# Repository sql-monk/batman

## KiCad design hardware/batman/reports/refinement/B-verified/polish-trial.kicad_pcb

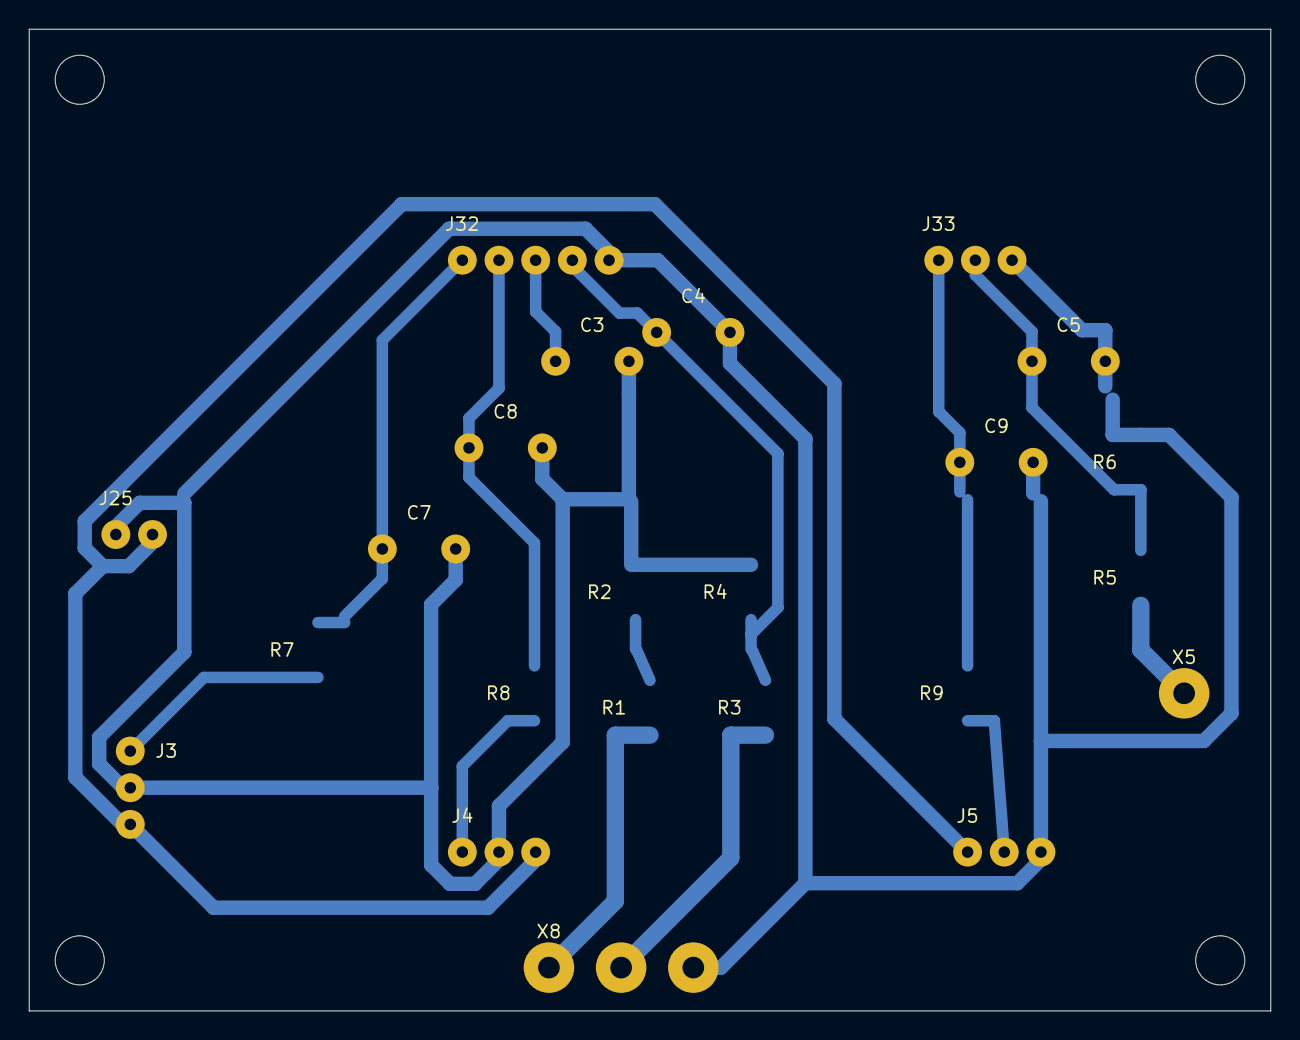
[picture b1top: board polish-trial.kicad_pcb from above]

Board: 2 copper layers, 86.0 x 68.0 mm, 28 parts (0 on the bottom side), 14 nets.

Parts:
C3: 100n_50V; LUT_C3
C4: 100n_50V; LUT_C4
C5: 100n_50V; LUT_C5
C7: 1u_16V; LUT_C7
C8: 1u_16V; LUT_C8
C9: 1u_16V; LUT_C9
HB1, HB2, HB3, HB4: M3_NPTH_3.4; Mount_M3
J3: ACS1_3WIRE; LUT_J3
J4: ACS2_3WIRE; LUT_J4
J5: ACS3_3WIRE; LUT_J5
J25: LINK_GND_+3V3_SENS; LUT_J25
J32: LINK_I_B1_I_B2_U_B1_U_B2_GND; LUT_J32
J33: LINK_I_LOAD_U_LOAD_GND; LUT_J33
R1: 100k_1%; LUT_R1
R2: 10k_1%; LUT_R2
R3: 100k_1%; LUT_R3
R4: 10k_1%; LUT_R4
R5: 100k_1%; LUT_R5
R6: 4.7k_1%; LUT_R6
R7: 1k; LUT_R7
R8: 1k; LUT_R8
R9: 1k; LUT_R9
WB1: INSULATED_WIRE; LUT_WB1
X5: U_LOAD_SENSE; LUT_X5
X8: BAT_SENSE_FROM_D; LUT_X8

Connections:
+3V3_SENS: J3.3, J4.3, J5.1, J25.2
B1: R1.1, X8.1
B2: R3.1, X8.2
GND: C3.2, C4.2, C5.2, C7.2, C8.2, C9.2, J3.2, J4.2, J5.3, J25.1, J32.5, J33.3, R2.2, R4.2, R6.2, X8.3
I_B1: C7.1, J32.1, R7.2
I_B2: C8.1, J32.2, R8.2
I_LOAD: C9.1, J33.1, R9.2
I_RAW1: J3.1, R7.1
I_RAW2: J4.1, R8.1
I_RAW3: J5.2, R9.1
LOAD+: R5.1, X5.1
U_B1: C3.1, J32.3, R1.2, R2.1, WB1.1
U_B2: C4.1, J32.4, R3.2, R4.1
U_LOAD: C5.1, J33.2, R5.2, R6.1

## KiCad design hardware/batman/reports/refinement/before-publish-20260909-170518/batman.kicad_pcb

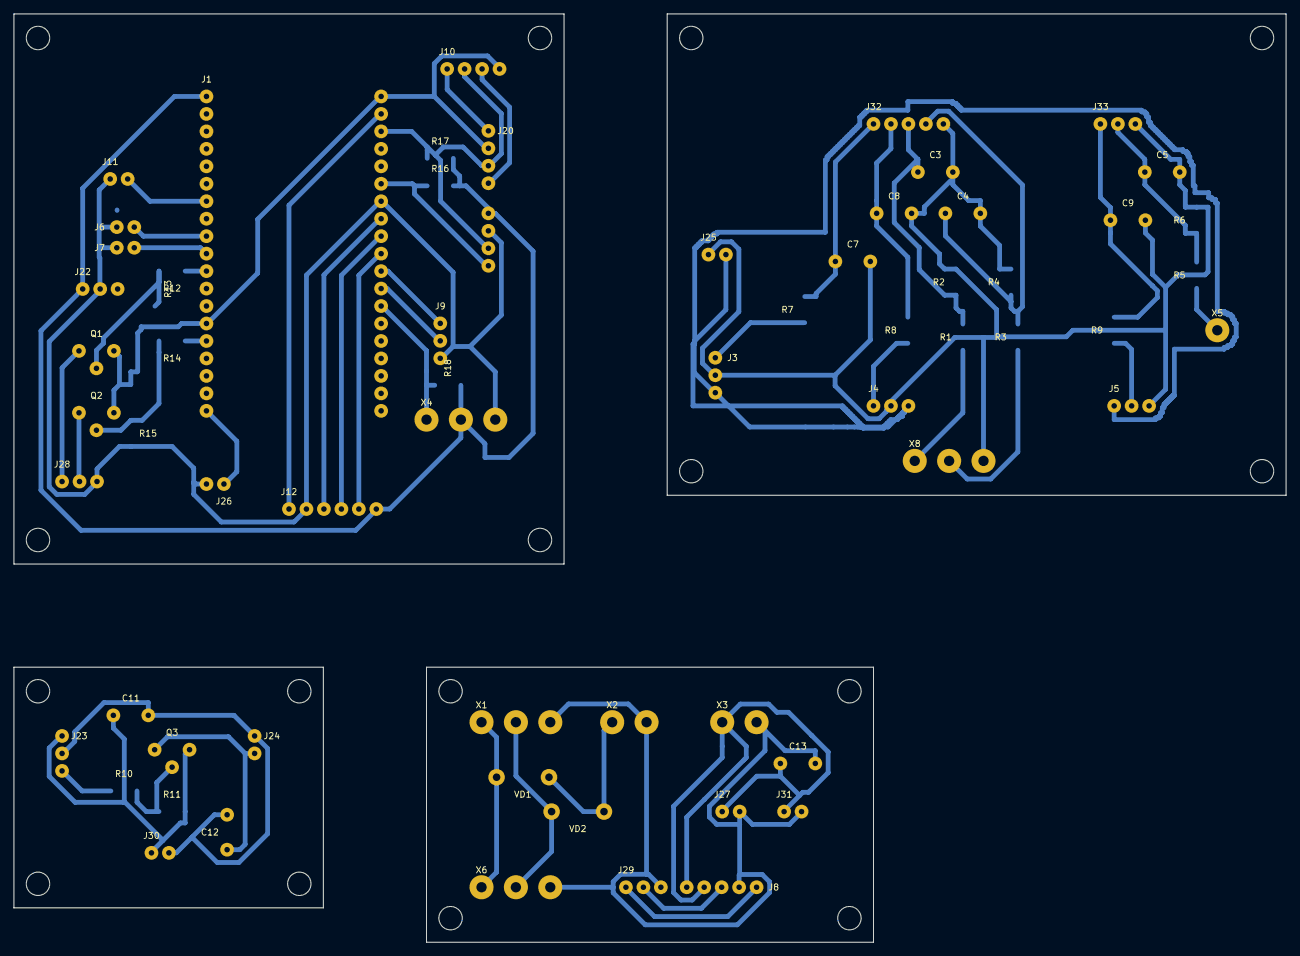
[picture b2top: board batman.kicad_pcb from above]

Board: 2 copper layers, 185.0 x 135.0 mm, 97 parts (0 on the bottom side), 39 nets.

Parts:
C3: 100n_50V; LUT_C3
C4: 100n_50V; LUT_C4
C5: 100n_50V; LUT_C5
C7: 1u_16V; LUT_C7
C8: 1u_16V; LUT_C8
C9: 1u_16V; LUT_C9
C11: 100n_16V; LUT_C11
C12: 100n_16V; LUT_C12
C13: 100n_16V; LUT_C13
HA1, HA2, HA3, HA4: M3_NPTH_3.4; Mount_M3
HB1, HB2, HB3, HB4: M3_NPTH_3.4; Mount_M3
HC1, HC2, HC3, HC4: M3_NPTH_3.4; Mount_M3
HD1, HD2, HD3, HD4: M3_NPTH_3.4; Mount_M3
J1: DevKitC_38_socket_mMCU; LUT_J1
J3: ACS1_3WIRE; LUT_J3
J4: ACS2_3WIRE; LUT_J4
J5: ACS3_3WIRE; LUT_J5
J6: SW1_GND_ON; LUT_J6
J7: SW2_GND_ON; LUT_J7
J8: RELAY; LUT_J8
J9: DPS_UART; LUT_J9
J10: OLED_I2C; LUT_J10
J11: BUTTON; LUT_J11
J12: SPI; LUT_J12
J20: LINK_+3V3_GND_SCL_SDA; LUT_J20
J21: LINK_+3V3_GND_SCL_SDA; LUT_J21
J22: LINK_+3V3_GND_SENS_PWR; LUT_J22
J23: LINK_+3V3_GND_SENS_PWR; LUT_J23
J24: LINK_GND_+3V3_SENS; LUT_J24
J25: LINK_GND_+3V3_SENS; LUT_J25
J26: LINK_+5V_GND; LUT_J26
J27: LINK_+5V_GND; LUT_J27
J28: LINK_RELAY_IN1_RELAY_IN2_GND; LUT_J28
J29: LINK_RELAY_IN1_RELAY_IN2_GND; LUT_J29
J30: LINK_+3V3_GND; LUT_J30
J31: LINK_+5V_GND; LUT_J31
J32: LINK_I_B1_I_B2_U_B1_U_B2_GND; LUT_J32
J33: LINK_I_LOAD_U_LOAD_GND; LUT_J33
NT1: COPPER_STAR_AT_X3; LUT_NT1
Q1: BC547_CBE; LUT_Q1
Q2: BC547_CBE; LUT_Q2
Q3: BC557_CBE; LUT_Q3
R1: 100k_1%; LUT_R1
R2: 10k_1%; LUT_R2
R3: 100k_1%; LUT_R3
R4: 10k_1%; LUT_R4
R5: 100k_1%; LUT_R5
R6: 4.7k_1%; LUT_R6
R7: 1k; LUT_R7
R8: 1k; LUT_R8
R9: 1k; LUT_R9
R10: 4.7k; LUT_R10
R11: 10k; LUT_R11
R12: 1k; LUT_R12
R13: 10k; LUT_R13
R14: 1k; LUT_R14
R15: 10k; LUT_R15
R16: 4.7k; LUT_R16
R17: 4.7k; LUT_R17
R18: 4.7k; LUT_R18
VD1: 1N5819; LUT_VD1
VD2: 1N5819; LUT_VD2
WA1: INSULATED_WIRE; LUT_WA1
WA2: INSULATED_WIRE; LUT_WA2
WA3: INSULATED_WIRE; LUT_WA3
WC2_1: EXTERNAL_CABLE_NOT_PCB; LUT_WC2_1
WC2_2: EXTERNAL_CABLE_NOT_PCB; LUT_WC2_2
WC2_3: EXTERNAL_CABLE_NOT_PCB; LUT_WC2_3
WC3_1: EXTERNAL_CABLE_NOT_PCB; LUT_WC3_1
WC3_2: EXTERNAL_CABLE_NOT_PCB; LUT_WC3_2
WC4_1: EXTERNAL_CABLE_NOT_PCB; LUT_WC4_1
WC4_2: EXTERNAL_CABLE_NOT_PCB; LUT_WC4_2
WC5_1: EXTERNAL_CABLE_NOT_PCB; LUT_WC5_1
WC5_2: EXTERNAL_CABLE_NOT_PCB; LUT_WC5_2
WC5_3: EXTERNAL_CABLE_NOT_PCB; LUT_WC5_3
WC6_1: EXTERNAL_CABLE_NOT_PCB; LUT_WC6_1
WC6_2: EXTERNAL_CABLE_NOT_PCB; LUT_WC6_2
WC6_3: EXTERNAL_CABLE_NOT_PCB; LUT_WC6_3
X1: B1_B2_GND; LUT_X1
X2: VIN_DC_GND; LUT_X2
X3: 5V_GND; LUT_X3
X4: DS18B20; LUT_X4
X5: U_LOAD_SENSE; LUT_X5
X6: BAT_SENSE_TO_B; LUT_X6
X8: BAT_SENSE_FROM_D; LUT_X8

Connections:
+3V3: C11.1, J1.1, J10.1, J12.6, J20.1, J21.1, J22.1, J23.1, J30.1, Q3.3, R11.2, R16.2, R17.2, R18.2, WA1.1, WC2_1.1, X4.2
+3V3_SENS: C12.1, J3.3, J4.3, J5.1, J24.2, J25.2, Q3.1, WC3_2.1
+5V: C13.1, J1.19, J26.1, J27.1, J31.1, NT1.1, WC4_1.1, X3.1
+5V_RELAY_COIL: J8.5, NT1.3
+5V_RELAY_VCC: J8.4, NT1.2
B1: R1.1, VD1.2, WC6_1.1, X1.1, X6.1, X8.1
B2: R3.1, VD2.2, WC6_2.1, X1.2, X6.2, X8.2
BASE1: Q1.2, R12.2, R13.1
BASE2: Q2.2, R14.2, R15.1
BASE3: Q3.2, R10.2, R11.1
BTN: J1.7, J11.2
CS: J1.29, J12.5
DPS_RX: J1.31, J9.2
DPS_TX: J1.30, J9.1
GND: C3.2, C4.2, C5.2, C7.2, C8.2, C9.2, C11.2, C12.2, C13.2, J1.14, J1.20, J1.26, J3.2, J4.2, J5.3, J6.1, J7.1, J8.2, J9.3, J10.4, J11.1, J12.2, J20.2, J21.2, J22.2, J23.2, J24.1, J25.1, J26.2, J27.2, J28.3, J29.3, J30.2, J31.2, J32.5, J33.3, Q1.3, Q2.3, R2.2, R4.2, R6.2, R13.2, R15.2, WC2_2.1, WC3_1.1, WC4_2.1, WC5_3.1, WC6_3.1, X1.3, X2.2, X3.2, X4.3, X6.3, X8.3
I_B1: C7.1, J32.1, R7.2
I_B2: C8.1, J32.2, R8.2
I_LOAD: C9.1, J33.1, R9.2
I_RAW1: J3.1, R7.1
I_RAW2: J4.1, R8.1
I_RAW3: J5.2, R9.1
K1: J1.11, R12.1
K2: J1.15, R14.1
LOAD+: R5.1, X5.1
MISO: J1.27, J12.3
MOSI: J1.21, J12.1
OW: J1.32, R18.1, X4.1
RELAY_IN1: J8.1, J28.1, J29.1, Q1.1, WC5_1.1
RELAY_IN2: J8.3, J28.2, J29.2, Q2.1, WC5_2.1
SCK: J1.28, J12.4
SCL: J1.22, J10.2, J20.3, J21.3, R17.1
SDA: J1.25, J10.3, J20.4, J21.4, R16.1, WA2.1
SENS_PWR: J1.12, J22.3, J23.3, R10.1, WA3.1, WC2_3.1
SW1_ON: J1.9, J6.2
SW2_ON: J1.10, J7.2
U_B1: C3.1, J32.3, R1.2, R2.1
U_B2: C4.1, J32.4, R3.2, R4.1
U_LOAD: C5.1, J33.2, R5.2, R6.1
VIN_DC: VD1.1, VD2.1, X2.1

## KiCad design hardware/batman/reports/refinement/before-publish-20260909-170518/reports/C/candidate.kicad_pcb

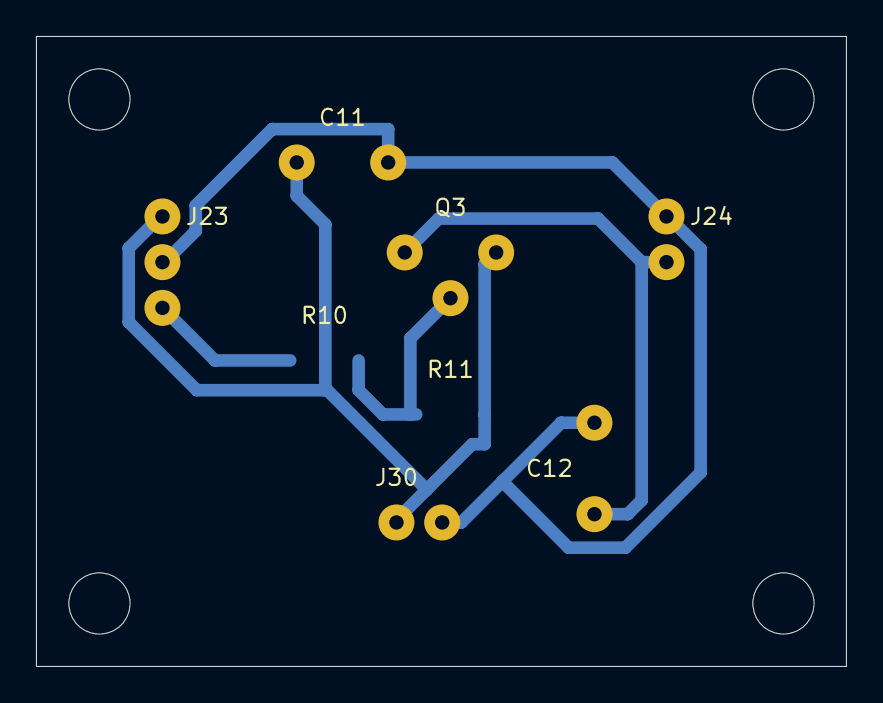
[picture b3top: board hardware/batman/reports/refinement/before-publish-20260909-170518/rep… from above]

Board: 2 copper layers, 45.0 x 35.0 mm, 12 parts (0 on the bottom side), 5 nets.

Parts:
C11: 100n_16V; LUT_C11
C12: 100n_16V; LUT_C12
HC1, HC2, HC3, HC4: M3_NPTH_3.4; Mount_M3
J23: LINK_+3V3_GND_SENS_PWR; LUT_J23
J24: LINK_GND_+3V3_SENS; LUT_J24
J30: LINK_+3V3_GND; LUT_J30
Q3: BC557_CBE; LUT_Q3
R10: 4.7k; LUT_R10
R11: 10k; LUT_R11

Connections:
+3V3: C11.1, J23.1, J30.1, Q3.3, R11.2
+3V3_SENS: C12.1, J24.2, Q3.1
BASE3: Q3.2, R10.2, R11.1
GND: C11.2, C12.2, J23.2, J24.1, J30.2
SENS_PWR: J23.3, R10.1

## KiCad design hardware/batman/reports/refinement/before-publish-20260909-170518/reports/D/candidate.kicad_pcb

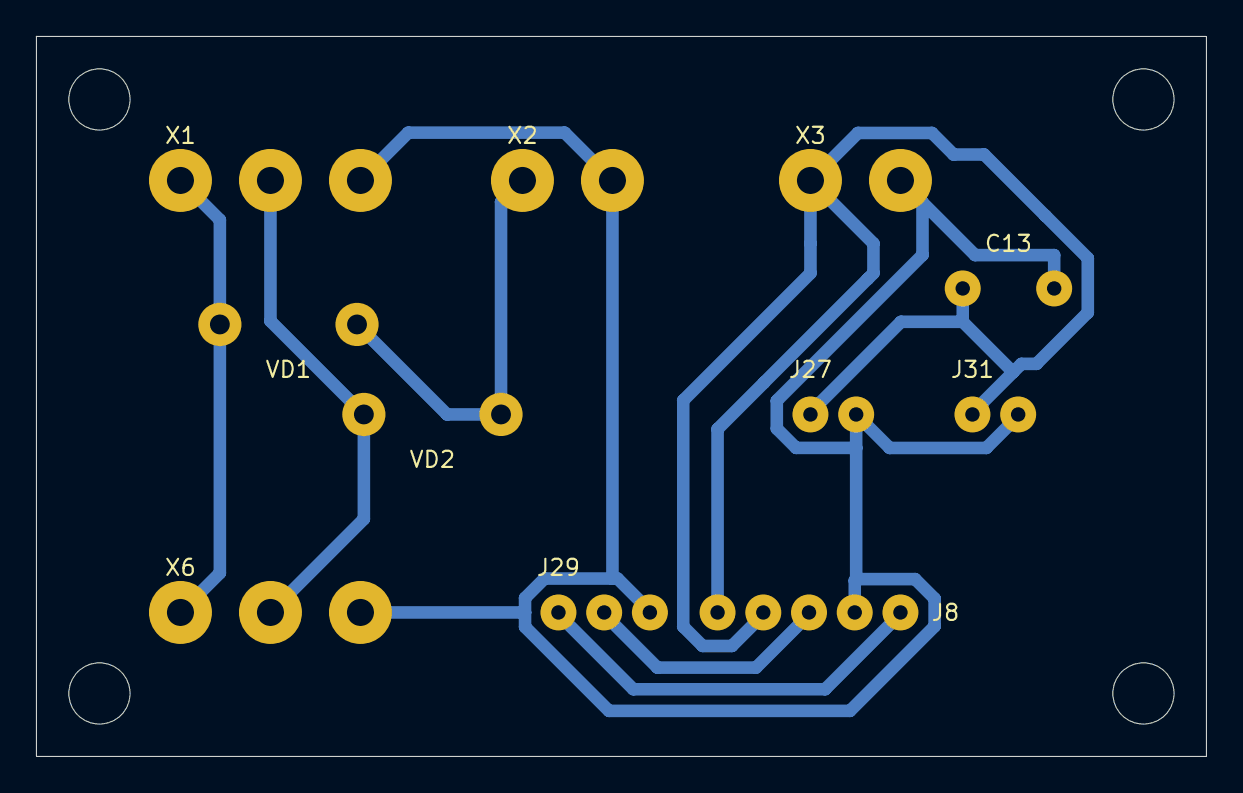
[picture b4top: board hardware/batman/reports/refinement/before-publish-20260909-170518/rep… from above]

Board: 2 copper layers, 65.0 x 40.0 mm, 16 parts (0 on the bottom side), 9 nets.

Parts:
C13: 100n_16V; LUT_C13
HD1, HD2, HD3, HD4: M3_NPTH_3.4; Mount_M3
J8: RELAY; LUT_J8
J27: LINK_+5V_GND; LUT_J27
J29: LINK_RELAY_IN1_RELAY_IN2_GND; LUT_J29
J31: LINK_+5V_GND; LUT_J31
NT1: COPPER_STAR_AT_X3; LUT_NT1
VD1: 1N5819; LUT_VD1
VD2: 1N5819; LUT_VD2
X1: B1_B2_GND; LUT_X1
X2: VIN_DC_GND; LUT_X2
X3: 5V_GND; LUT_X3
X6: BAT_SENSE_TO_B; LUT_X6

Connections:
+5V: C13.1, J27.1, J31.1, NT1.1, X3.1
+5V_RELAY_COIL: J8.5, NT1.3
+5V_RELAY_VCC: J8.4, NT1.2
B1: VD1.2, X1.1, X6.1
B2: VD2.2, X1.2, X6.2
GND: C13.2, J8.2, J27.2, J29.3, J31.2, X1.3, X2.2, X3.2, X6.3
RELAY_IN1: J8.1, J29.1
RELAY_IN2: J8.3, J29.2
VIN_DC: VD1.1, VD2.1, X2.1
